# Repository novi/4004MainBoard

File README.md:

[周辺回路(ROM, IO)](https://github.com/novi/4004Peripheral)

TODO:

* たまにリセットが効かないことがある(手動リセットすること)
* バッファドライバの改善

## See Also

* [jim11662418/4004-SBC](https://github.com/jim11662418/4004-SBC)
* [MCS-4 Test Boards for Sale](https://www.cpushack.com/mcs-4-test-boards-for-sale/)
* [Intel 4004 — 50th Anniversary Project](https://www.4004.com)
* [Intel 4004 system](http://dangerousprototypes.com/forum/index.php?topic=4721.0)
* [MCS-4](http://www.st.rim.or.jp/~nkomatsu/intel4bit/i4004.html)
* [佐野正博「世界最初のマイクロプロセッサ Intel 4004」](https://www.sanosemi.com/document/Intel_4004_Ver4-2.pdf)
* [Intel 4004の回路図を読む](http://www.gc-net.jp/omiokone/mcs4/index.htm)
* [マイクロプロセッサ 4004 の開発](https://www.shmj.or.jp/dev_story/pdf/develop43.pdf)

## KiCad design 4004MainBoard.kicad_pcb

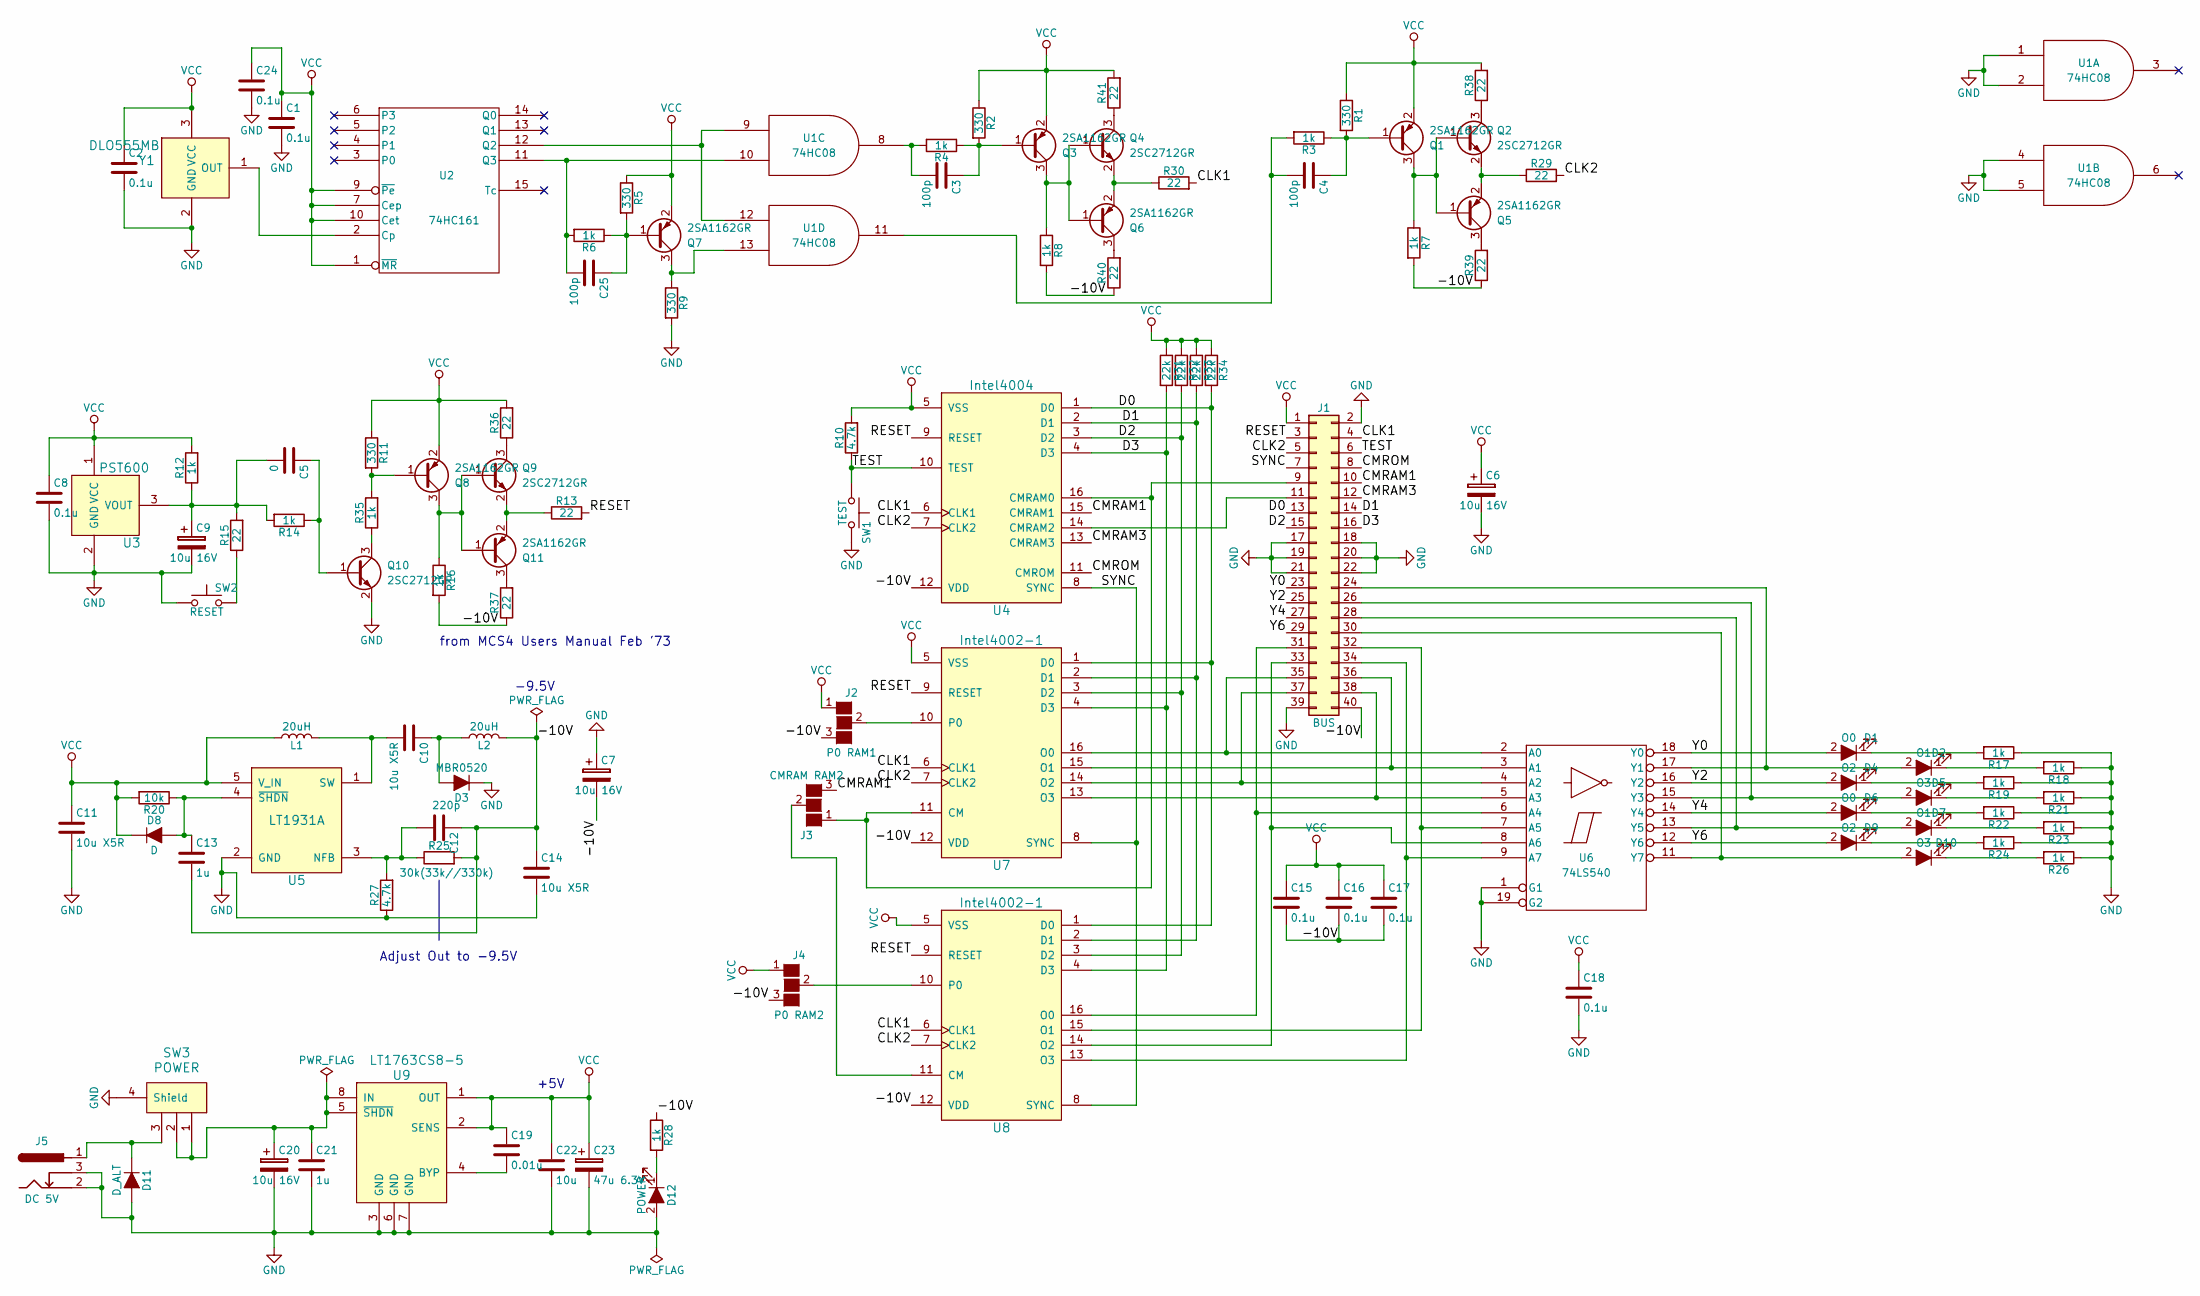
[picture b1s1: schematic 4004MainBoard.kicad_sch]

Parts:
C1, C2, C8, C15, C16, C17, C18, C24: 0.1u; C_0603_1608Metric_Pad1.08x0.95mm_HandSolder
C3, C4, C25: 100p; C_0603_1608Metric_Pad1.08x0.95mm_HandSolder
C5: 0; C_0603_1608Metric_Pad1.08x0.95mm_HandSolder
C6, C7, C9, C20: 10u 16V; CP_Elec_4x4.5
C10, C11, C14: 10u X5R; C_1206_HandSoldering
C12: 220p; C_0603_1608Metric_Pad1.08x0.95mm_HandSolder
C13, C21: 1u; C_0603_1608Metric_Pad1.08x0.95mm_HandSolder
C19: 0.01u; C_0603_1608Metric_Pad1.08x0.95mm_HandSolder
C22: 10u; C_1206_HandSoldering
C23: 47u 6.3V; CP_Elec_5x5.8
D1, D6: O0; LED_0603_HandSoldering
D2, D7: O1; LED_0603_HandSoldering
D3: MBR0520; D_SOD-123_HandSoldering
D4, D9: O2; LED_0603_HandSoldering
D5, D10: O3; LED_0603_HandSoldering
D8: D; D_SOD-123_HandSoldering
D11: D_ALT; D_SOD-123_HandSoldering
D12: POWER; LED_0603_HandSoldering
J1: BUS; Pin_Header_Straight_2x20_Pitch2.54mm
J2: P0 RAM1; GS3
J3: CMRAM RAM2; GS3
J4: P0 RAM2; GS3
J5: DC 5V; DC_JACK_MJ-179PH
L1, L2: 20uH; Choke_SMD_10.4x10.4_H4.8
Q1, Q3, Q5, Q6, Q7, Q8, Q11: 2SA1162GR; SC-59_Handsoldering
Q2, Q4, Q9, Q10: 2SC2712GR; SC-59_Handsoldering
R1, R2, R5, R9, R11: 330; R_0603_1608Metric_Pad0.98x0.95mm_HandSolder
R3, R4, R6, R7, R8, R12, R14, R16, R17, R18, R19, R21, R22, R23, R24, R26, R28, R35: 1k; R_0603_1608Metric_Pad0.98x0.95mm_HandSolder
R10, R27: 4.7k; R_0603_1608Metric_Pad0.98x0.95mm_HandSolder
R13, R15, R29, R30, R36, R37, R38, R39, R40, R41: 22; R_0603_1608Metric_Pad0.98x0.95mm_HandSolder
R20: 10k; R_0603_1608Metric_Pad0.98x0.95mm_HandSolder
R25: 30k(33k//330k); R_0603_1608Metric_Pad0.98x0.95mm_HandSolder
R31, R32, R33, R34: 22k; R_0603_1608Metric_Pad0.98x0.95mm_HandSolder
SW1: TEST; SW_PUSH_6mm
SW2: RESET; SW_PUSH_6mm
SW3: POWER; ToggleSW_MS-612A_RI
U1: 74HC08; SOIC-14_3.9_5.3x8.7mm_P1.27mm
U2: 74HC161; SOIC-16_3.9_5.3x10.2mm_P1.27mm
U3: PST600; TO-92_Inline_Wide
U4: Intel4004; DIP-16_W7.62mm_Socket
U5: LT1931A; TSOT-23-5_HandSoldering
U6: 74LS540; SOIC-20W_7.5x12.8mm_Pitch1.27mm
U7, U8: Intel4002-1; DIP-16_W7.62mm_Socket
U9: LT1763CS8-5; SOIC-8_3.9x4.9mm_Pitch1.27mm
Y1: DLO555MB; TO-92_Inline_Wide

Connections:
/-10V: C7.2, C12.1, C13.2, C14.1, C15.2, C16.2, C17.2, J1.40, J2.3 (G3), J4.3 (G3), L2.2, R7.2, R8.2, R16.2, R25.2, R28.1, R37.1, R39.1, R40.1, U4.12 (VDD), U7.12 (VDD), U8.12 (VDD)
/CLK1: J1.4, R30.2, U4.6 (CLK1), U7.6 (CLK1), U8.6 (CLK1)
/CLK2: J1.5, R29.2, U4.7 (CLK2), U7.7 (CLK2), U8.7 (CLK2)
/CMRAM1: J1.10, J3.3 (G3), U4.15 (CMRAM1)
/CMRAM3: J1.12, U4.13 (CMRAM3)
/CMROM: J1.8, U4.11 (CMROM)
/D0: J1.13, R34.2, U4.1 (D0), U7.1 (D0), U8.1 (D0)
/D1: J1.14, R33.2, U4.2 (D1), U7.2 (D1), U8.2 (D1)
/D2: J1.15, R32.2, U4.3 (D2), U7.3 (D2), U8.3 (D2)
/D3: J1.16, R31.2, U4.4 (D3), U7.4 (D3), U8.4 (D3)
/RESET: J1.3, R13.2, U4.9 (RESET), U7.9 (RESET), U8.9 (RESET)
/SYNC: J1.7, U4.8 (SYNC), U7.8 (SYNC), U8.8 (SYNC)
/TEST: J1.6, R10.1, SW1.1, U4.10 (TEST)
/Y0: D1.2 (A), J1.23, U6.18 (Y0)
/Y2: D4.2 (A), J1.25, U6.16 (Y2)
/Y4: D6.2 (A), J1.27, U6.14 (Y4)
/Y6: D9.2 (A), J1.29, U6.12 (Y6)
GND: C1.2, C2.2, C6.2, C7.1, C8.2, C9.2, C11.2, C14.2, C18.2, C20.2, C21.2, C22.2, C23.2, C24.2, D3.1 (K), D11.2 (A), D12.2 (A), J1.2, J1.17, J1.18, J1.19, J1.20, J1.21, J1.22, J1.39, J5.2, J5.3, Q10.2 (E), R9.2, R17.1, R18.1, R19.1, R21.1, R22.1, R23.1, R24.1, R26.1, R27.1, SW1.2, SW2.1, SW3.4 (Shield), U1.1, U1.2, U1.4, U1.5, U1.7 (GND), U2.8 (GND), U3.2 (GND), U5.2 (GND), U6.1 (G1), U6.10 (GND), U6.19 (G2), U9.3 (GND), U9.6 (GND), U9.7 (GND), Y1.2 (GND)
unnamed: C3.2, R4.2, U1.8
unnamed: C4.2, R3.2, U1.11
unnamed: D1.1 (K), R17.2
unnamed: D2.2 (A), J1.24, U6.17 (Y1)
unnamed: D2.1 (K), R18.2
unnamed: C10.1, D3.2 (A), L2.1
unnamed: D4.1 (K), R19.2
unnamed: D5.2 (A), J1.26, U6.15 (Y3)
unnamed: D5.1 (K), R21.2
unnamed: D6.1 (K), R22.2
unnamed: D7.2 (A), J1.28, U6.13 (Y5)
unnamed: D7.1 (K), R23.2
unnamed: C13.1, D8.2 (A), R20.1, U5.4 (~SHDN)
unnamed: D9.1 (K), R24.2
unnamed: D10.2 (A), J1.30, U6.11 (Y7)
unnamed: D10.1 (K), R26.2
unnamed: D11.1 (K), J5.1, SW3.3
unnamed: D12.1 (K), R28.2
unnamed: J1.9, J3.1 (G1), U4.16 (CMRAM0), U7.11 (CM)
unnamed: J1.11, U4.14 (CMRAM2)
unnamed: J1.31, U6.6 (A4), U8.16 (O0)
unnamed: J1.32, U6.7 (A5), U8.15 (O1)
unnamed: J1.33, U6.8 (A6), U8.14 (O2)
unnamed: J1.34, U6.9 (A7), U8.13 (O3)
unnamed: J1.35, U6.2 (A0), U7.16 (O0)
unnamed: J1.36, U6.3 (A1), U7.15 (O1)
unnamed: J1.37, U6.4 (A2), U7.14 (O2)
unnamed: J1.38, U6.5 (A3), U7.13 (O3)
unnamed: J2.2 (G2), U7.10 (P0)
unnamed: J3.2 (G2), U8.11 (CM)
unnamed: J4.2 (G2), U8.10 (P0)
unnamed: C4.1, Q1.1 (B), R1.2, R3.1
unnamed: Q1.3 (C), Q2.1 (B), Q5.1 (B), R7.1
unnamed: Q2.3 (C), R38.1
unnamed: Q2.2 (E), Q5.2 (E), R29.1
unnamed: C3.1, Q3.1 (B), R2.2, R4.1
unnamed: Q3.3 (C), Q4.1 (B), Q6.1 (B), R8.1
unnamed: Q4.3 (C), R41.1
unnamed: Q4.2 (E), Q6.2 (E), R30.1
unnamed: Q5.3 (C), R39.2
unnamed: Q6.3 (C), R40.2
unnamed: C25.1, Q7.1 (B), R5.2, R6.1
unnamed: Q7.3 (C), R9.1, U1.13
unnamed: Q8.1 (B), R11.2, R35.2
unnamed: Q9.3 (C), R36.1
unnamed: C5.1, Q10.1 (B), R14.1
unnamed: Q10.3 (C), R35.1
unnamed: Q8.3 (C), Q9.1 (B), Q11.1 (B), R16.1
unnamed: Q11.3 (C), R37.2
unnamed: Q9.2 (E), Q11.2 (E), R13.1
unnamed: R15.1, SW2.2
unnamed: U2.2 (Cp), Y1.1 (OUT)
unnamed: U1.9, U1.12, U2.12 (Q2)
unnamed: C25.2, R6.2, U1.10, U2.11 (Q3)
unnamed: C5.2, C9.1, R12.1, R14.2, R15.2, U3.3 (VOUT)
unnamed: C12.2, R25.1, R27.2, U5.3 (NFB)
unnamed: C10.2, L1.2, U5.1 (SW)
unnamed: C19.2, U9.4 (BYP)
unnamed: C20.1, C21.1, SW3.1, SW3.2, U9.5 (~SHDN), U9.8 (IN)
VCC: C1.1, C2.1, C6.1, C8.1, C11.1, C15.1, C16.1, C17.1, C18.1, C19.1, C22.1, C23.1, C24.1, D8.1 (K), J1.1, J2.1 (G1), J4.1 (G1), L1.1, Q1.2 (E), Q3.2 (E), Q7.2 (E), Q8.2 (E), R1.1, R2.1, R5.1, R10.2, R11.1, R12.2, R20.2, R31.1, R32.1, R33.1, R34.1, R36.2, R38.2, R41.2, U1.14 (VCC), U2.1 (~MR), U2.7 (Cep), U2.9 (~Pe), U2.10 (Cet), U2.16 (VCC), U3.1 (VCC), U4.5 (VSS), U5.5 (V_IN), U6.20 (VCC), U7.5 (VSS), U8.5 (VSS), U9.1 (OUT), U9.2 (SENS), Y1.3 (VCC)

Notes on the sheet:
Adjust Out to -9.5V
+5V
from MCS4 Users Manual Feb '73
-9.5V

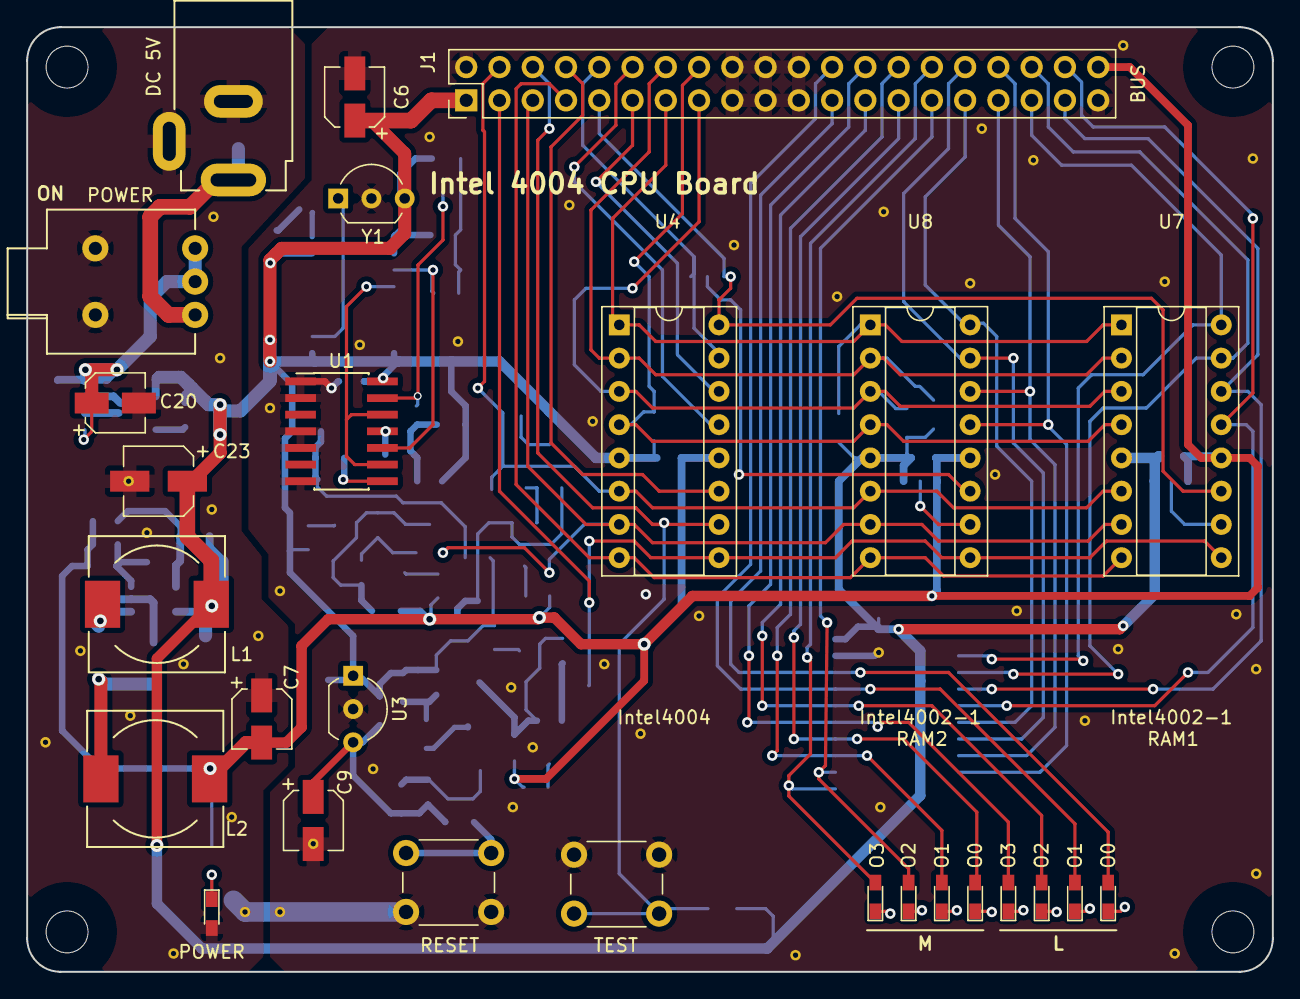
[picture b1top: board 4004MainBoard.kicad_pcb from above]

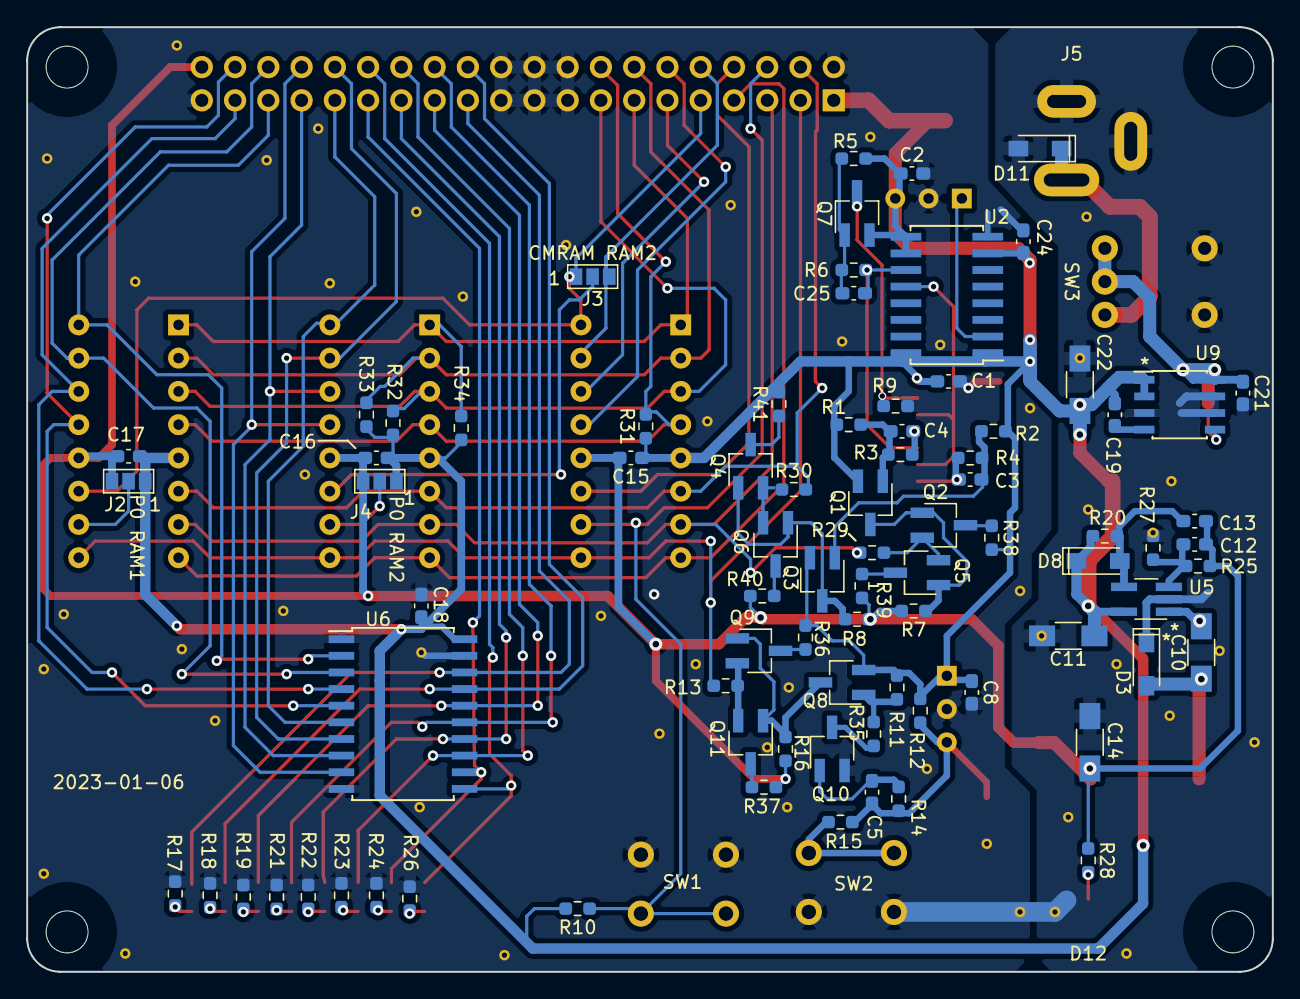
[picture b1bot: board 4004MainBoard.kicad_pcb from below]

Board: 2 copper layers, 95.1 x 72.1 mm, 109 parts (82 on the bottom side), 78 nets.

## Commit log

2018-01-21 回路を実装
2018-05-03 パターンを実装
2018-05-04 パターン修正 ビア実装
2018-05-13 回路修正 シルク修正
2018-06-24 電源電圧調整 基板修正
2021-03-12 整理時コミット
2022-10-07 add LICENSE
2022-10-07 migrate to KiCad 6
2022-10-07 add README
2024-01-06 migrate to KiCad 7
2024-04-15 update descrete buffer add notes
